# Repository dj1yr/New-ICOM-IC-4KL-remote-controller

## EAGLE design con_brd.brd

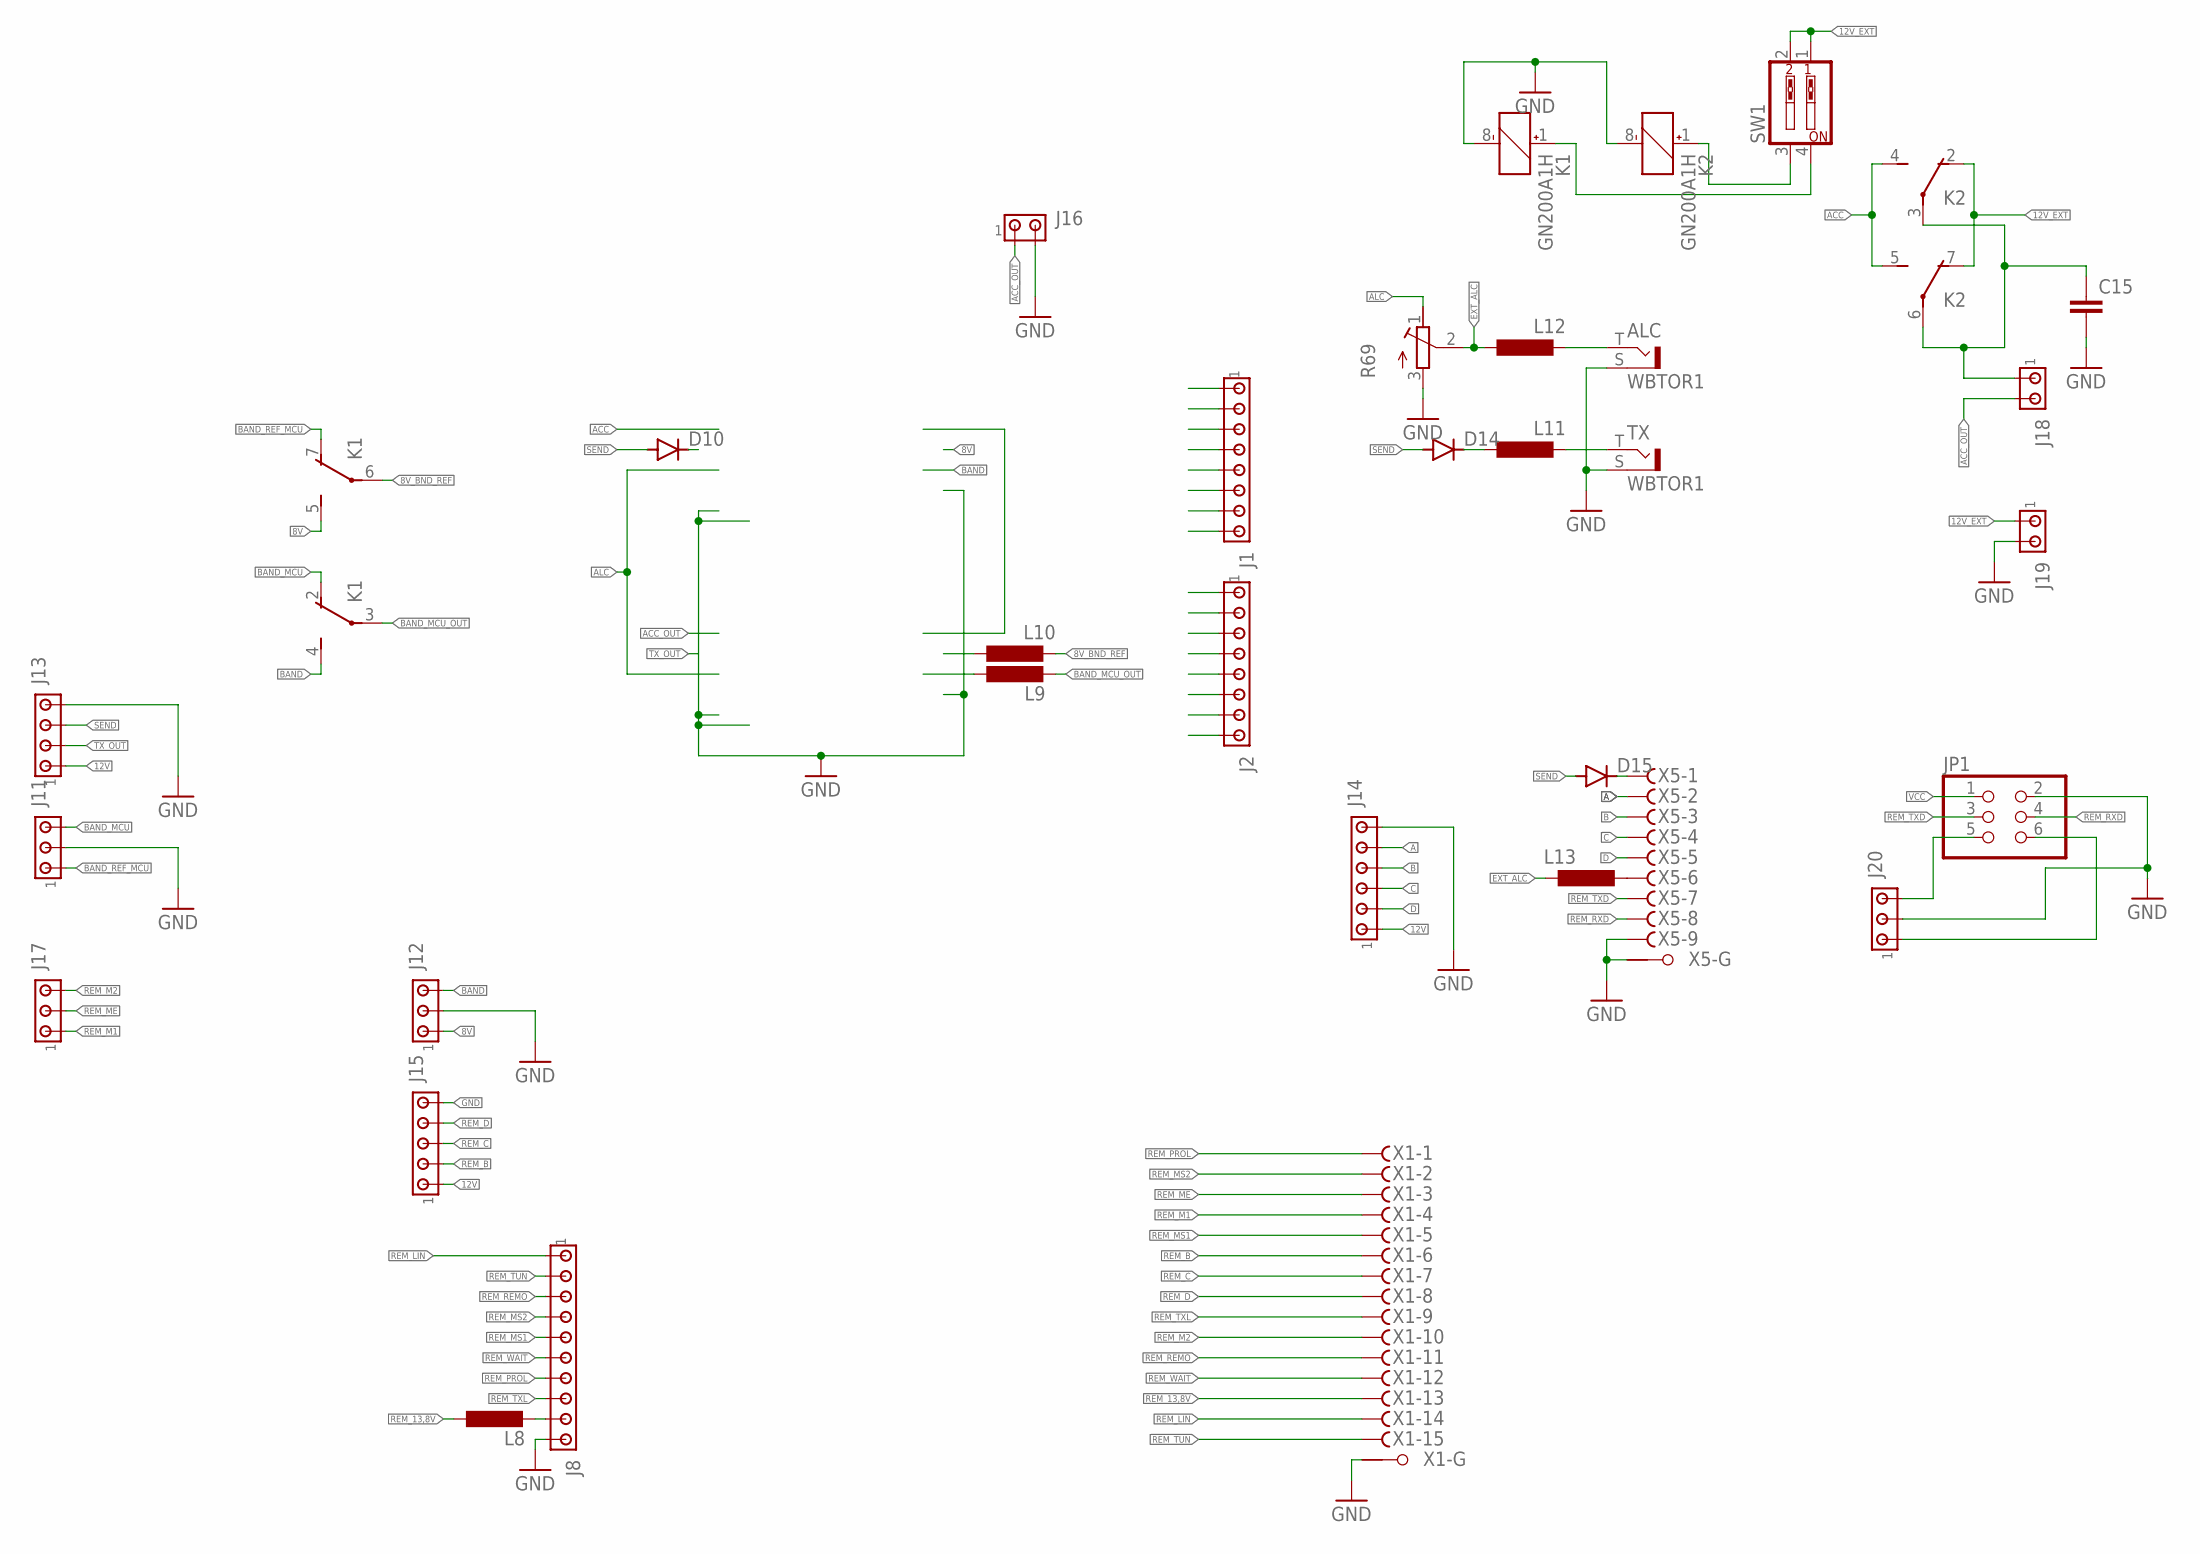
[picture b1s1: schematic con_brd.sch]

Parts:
ALC: WBTOR1
C15: C-EUC0805K; C0805K
D10, D14, D15: DIODE-SOD123; SOD123
J1, J2: MTA08-100; 10X08MTA
J8: MTA10-100; 10X10MTA
J11, J12, J17, J20: MTA03-100; 10X03MTA
J13: MTA04-100; 10X04MTA
J14: MTA06-100; 10X06MTA
J15: MTA05-100; 10X05MTA
J16, J18, J19: MTA02-100; 10X02MTA
JP1: PINHD-2X3; 2X03
K1, K2: GN200A1H; GN-A
L8: L-EUL3230M; L3230M
L9, L10, L11, L12, L13: L-EUL2012C; L2012C
R69: R-TRIMM43P; RTRIM43P
SW1: SW_DIP-2; EDG-02
TX: WBTOR1
X1: F15HPS; F15HP
X5: F09HPS; F09HP

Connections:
8V: J1.1, J12.1, K1.5 (S)
8V_BND_REF: K1.6, L10.2
12V: J13.1, J14.1, J15.1
12V_EXT: J19.1, K2.2 (O), K2.7 (O), SW1.1, SW1.2
A: J14.5, X5.2 (F)
ACC: J1.7, K2.4 (S), K2.5 (S)
ACC_OUT: J2.7, J16.1, J18.2
ALC: J1.5, J2.5, R69.1 (E)
B: J14.4, X5.3 (F)
BAND: J1.4, J12.3, K1.4 (S)
BAND_MCU: J11.3, K1.2 (O)
BAND_MCU_OUT: K1.3, L9.2
BAND_REF_MCU: J11.1, K1.7 (O)
C: J14.3, X5.4 (F)
D: J14.2, X5.5 (F)
EXT_ALC: L12.1, L13.1, R69.2 (S)
GND: ALC.S, C15.2, J1.2, J1.8, J2.2, J2.8, J8.10, J11.2, J12.2, J13.4, J14.6, J15.5, J16.2, J19.2, J20.2, JP1.2, K1.8 (-), K2.8 (-), R69.3 (A), TX.S, X1.G1, X5.9 (F), X5.G1; also elsewhere on the board
unnamed: J1.6, J2.6
unnamed: J2.4, L9.1
unnamed: J2.1, L10.1
unnamed: L11.2, TX.T
unnamed: ALC.T, L12.2
unnamed: D10.C, J1.3
unnamed: D14.C, L11.1
unnamed: D15.C, X5.1 (F)
unnamed: L13.2, X5.6 (F)
unnamed: J20.3, JP1.5
unnamed: J8.9, L8.2
unnamed: K2.1 (+), SW1.3
unnamed: K1.1 (+), SW1.4
unnamed: J20.1, JP1.6
REM_13,8V: L8.1, X1.13 (F)
REM_B: J15.2, X1.6 (F)
REM_C: J15.3, X1.7 (F)
REM_D: J15.4, X1.8 (F)
REM_LIN: J8.1, X1.14 (F)
REM_M1: J17.1, X1.4 (F)
REM_M2: J17.3, X1.10 (F)
REM_ME: J17.2, X1.3 (F)
REM_MS1: J8.5, X1.5 (F)
REM_MS2: J8.4, X1.2 (F)
REM_PROL: J8.7, X1.1 (F)
REM_REMO: J8.3, X1.11 (F)
REM_RXD: JP1.4, X5.8 (F)
REM_TUN: J8.2, X1.15 (F)
REM_TXD: JP1.3, X5.7 (F)
REM_TXL: J8.8, X1.9 (F)
REM_WAIT: J8.6, X1.12 (F)
SEND: D10.A, D14.A, D15.A, J13.3
TX_OUT: J2.3, J13.2
VCC: C15.1, J18.1, JP1.1, K2.3, K2.6

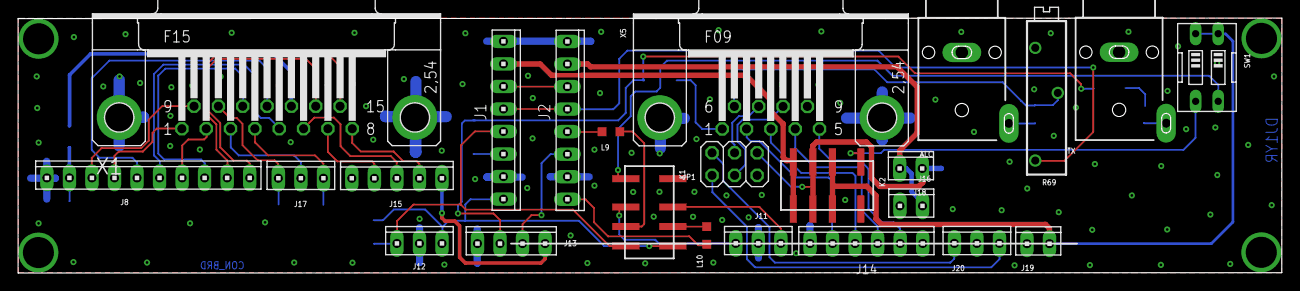
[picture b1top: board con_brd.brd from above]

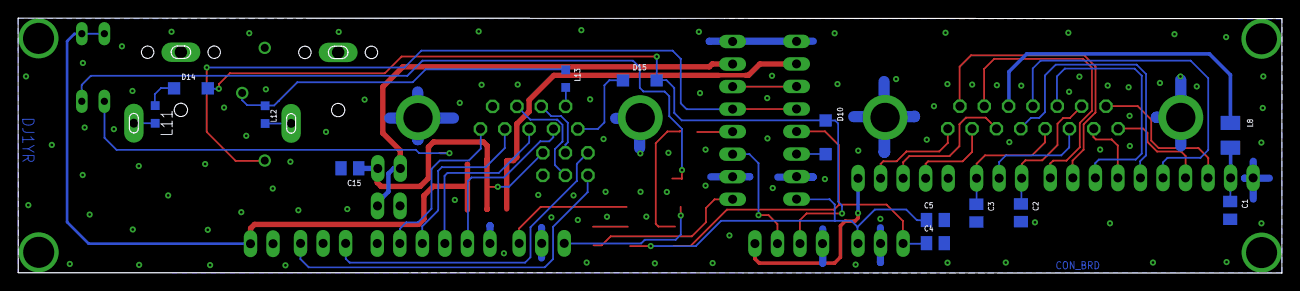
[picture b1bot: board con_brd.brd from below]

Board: 2 copper layers, 142.4 x 28.7 mm, 37 parts (13 on the bottom side), 51 nets.

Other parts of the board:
C1, C2, C3, C4, C5: C0805K

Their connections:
GND: C1.2, C2.2, C3.2, C4.2, C5.2; also elsewhere on the board

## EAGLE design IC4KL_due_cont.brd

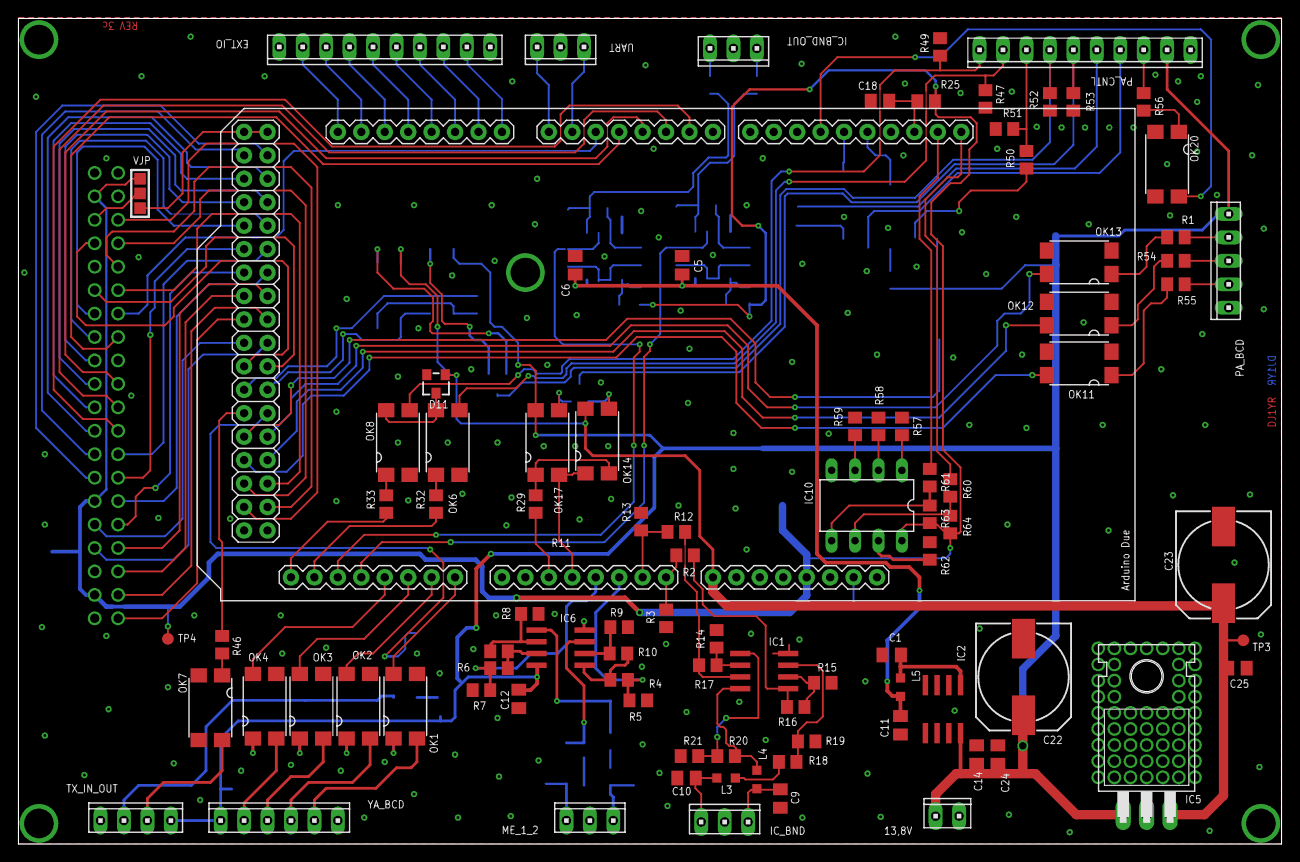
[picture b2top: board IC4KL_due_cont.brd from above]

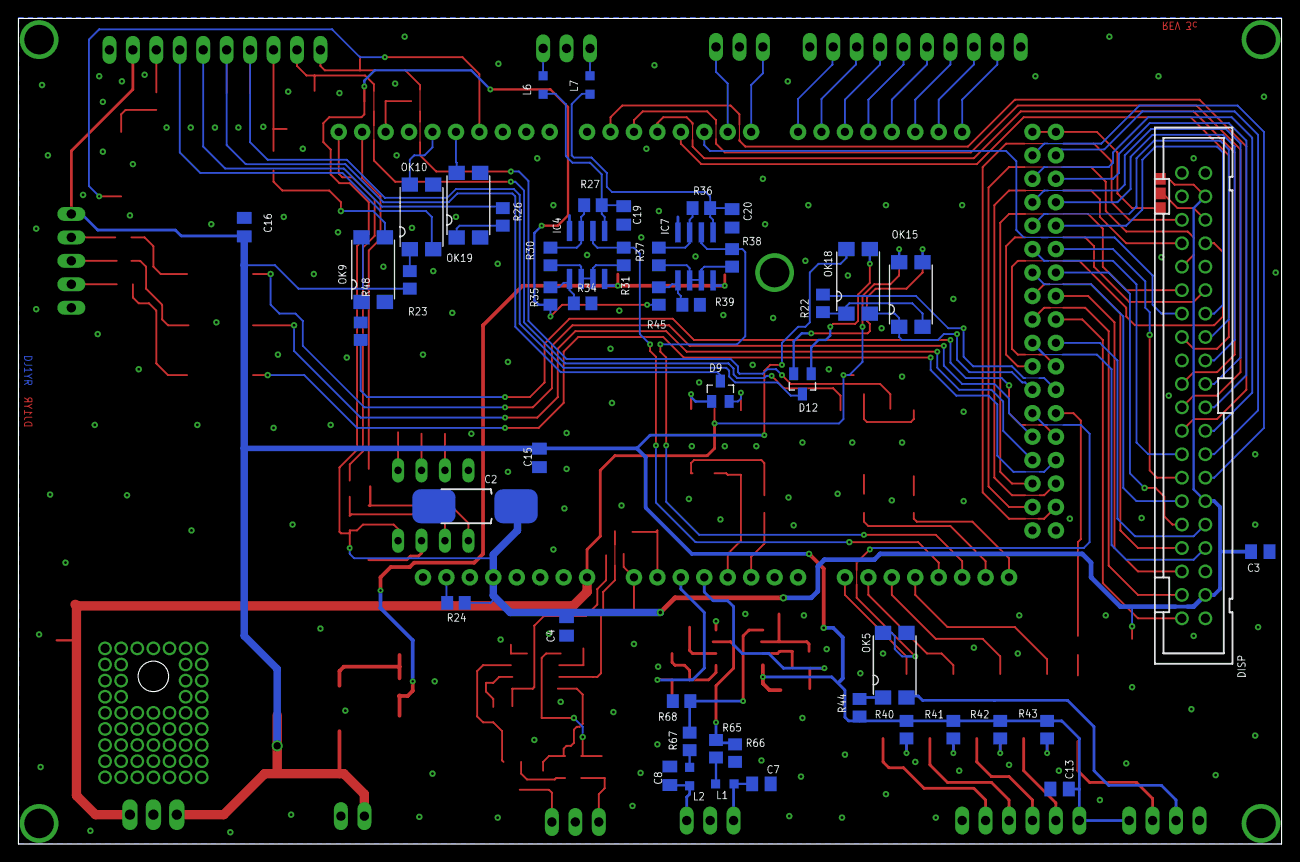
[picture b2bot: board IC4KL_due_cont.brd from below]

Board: 2 copper layers, 136.9 x 89.4 mm, 139 parts (49 on the bottom side), 92 nets.

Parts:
13,8V: 10X02MTA
C1, C3, C4, C5, C6, C7, C8, C9, C10, C11, C12, C13, C14, C15, C16, C18, C19, C20, C24, C25: C0805K
C2: 085CS_1AW
C22, C23: 150CLZ-1010
D9, D12: SOT23
D11: BZX84CSMD; TO236
DISP: 2540-; PAK100/2500-40
EXT_IO: 10X10MTA
IC1, IC4, IC6, IC7: LM358D; SO08
IC2: 78L10SMD; SO08
IC5: 7805T; TO220H
IC10: AT24CP; DIL08
IC_BND: 10X03MTA
IC_BND_OUT: 10X03MTA
L1, L2, L3, L4, L5, L6, L7: L2012C
ME_1_2: 10X03MTA
OK1, OK2, OK3, OK4, OK5, OK6, OK7, OK8, OK9, OK10, OK11, OK12, OK13, OK14, OK15, OK17, OK18, OK19, OK20: SFH6186-3; SMD4
PA_BCD: 10X05MTA
PA_CNTL: 10X10MTA
R1, R2, R4, R6, R10, R11, R12, R16, R17, R18, R20, R22, R23, R26, R29, R32, R33, R40, R41, R42, R43, R44, R48, R54, R55, R56, R57, R58, R59, R60, R61, R62, R63, R64, R65, R67: 1k; R0805
R3, R5, R7, R13: 1.8k; R0805
R8, R9, R14, R15: 220k; R0805
R19, R21: 10k; R0805
R24, R25, R50: 10; R0805
R27, R31, R36, R38, R47, R49, R51, R52, R53: 100k; R0805
R30, R34, R35, R37, R39, R45: 22k; R0805
R46: 390R; R0805
R66, R68: 2k2; R0805
TP3, TP4: TPB1,27; B1,27
TX_IN_OUT: 10X04MTA
UART: 10X03MTA
YA_BCD: 10X06MTA

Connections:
3.3V: C2.+, C3.1, C4.1, DISP.3, DISP.11, DISP.37, IC10.8, R24.2, R25.1, R35.1, R45.1, R63.2, R64.2, TP4.TP
5VIN: C23.+, C25.1, D11.A, DISP.35, IC5.3, OK14.4, OK15.4, TP3.TP
10V_BND_OPV: C5.1, C6.1, IC1.8, IC4.8, IC7.8
12V: 13,8V.2, C12.2, C13.2, C14.1, C15.2, C16.2, C22.+, C24.1, EXT_IO.1, IC2.8, IC5.1, IC6.8, OK9.4, OK17.4, OK18.4, PA_BCD.1, PA_CNTL.9, R23.1, R40.2, R41.2, R42.2, R43.2, R44.2, TX_IN_OUT.1, YA_BCD.6
DAC_IC_BND_OUT: IC4.2, R31.1
DAC_IC_BND_REF_OUT: IC7.2, R38.1
GND: 13,8V.1, C1.2, C2.-, C3.2, C4.2, C5.2, C6.2, C7.1, C8.2, C9.2, C10.1, C11.2, C12.1, C13.1, C14.2, C15.1, C16.1, C18.1, C19.2, C20.2, C22.-, C23.-, C24.2, C25.2, DISP.1, EXT_IO.10, IC1.4, IC2.2, IC2.3, IC2.6, IC2.7, IC4.4, IC5.2, IC6.4, IC7.4, IC10.4, IC_BND.2, IC_BND_OUT.2, ME_1_2.2, OK1.3, OK2.3, OK3.3, OK4.3, OK5.3, OK6.2, OK7.2, OK7.3, OK8.2, OK9.2, OK10.3, OK11.2, OK11.3, OK12.2, OK12.3, OK13.2, OK13.3, OK19.2, OK19.3, OK20.2, OK20.3, PA_BCD.5, PA_CNTL.10, R3.1, R5.1, R7.2, R8.2, R9.2, R13.2, R14.2, R15.2, R19.1, R21.1, R34.2, R39.2, R47.2, R49.2, R51.2, R52.2, R53.2, R57.1, R58.1, R59.1, R62.1, R66.1, R68.1, TX_IN_OUT.4, UART.2, YA_BCD.1
IC_BND: R2.1, R3.2
IC_BND_IN: C10.2, IC_BND.3, L3.1
IC_BND_OUT: IC_BND_OUT.3, L6.2
IC_BND_REF_IN: C9.1, IC_BND.1, L4.1
IC_BND_REF_OUT: IC_BND_OUT.1, L7.2
LINEAR: OK8.3, PA_CNTL.1, R49.1
M1: C7.2, L1.1, ME_1_2.3
M2: C8.1, L2.1, ME_1_2.1
ME1: R4.1, R5.2
ME2: R6.1, R7.1
MS1: D9.3, PA_CNTL.5, R53.1
MS2: D12.3, PA_CNTL.4, R52.1
unnamed: L2.2, R67.2
unnamed: IC6.1, R4.2, R10.2
unnamed: OK1.1, R40.1
unnamed: L1.2, R65.1
unnamed: IC6.7, R6.2, R11.2
unnamed: IC6.6, R8.1, R11.1
unnamed: IC6.2, R9.1, R10.1
unnamed: OK13.1, R1.1
unnamed: PA_BCD.2, R1.2
unnamed: IC1.1, R2.2, R16.2
unnamed: IC1.7, R12.2, R17.2
unnamed: IC1.6, R14.1, R17.1
unnamed: IC1.2, R15.1, R16.1
unnamed: IC7.3, R36.2, R37.1
unnamed: IC1.3, R18.2, R19.2
unnamed: L4.2, R20.2
unnamed: L3.2, R18.1
unnamed: D12.1, OK18.3
unnamed: C1.1, IC2.1, L5.1
unnamed: OK6.1, R32.2
unnamed: OK8.1, R33.2
unnamed: D11.C, OK6.4, OK8.4
unnamed: IC4.3, R27.2, R30.1
unnamed: OK15.2, OK18.1, R22.1
unnamed: IC1.5, R20.1, R21.2
unnamed: C19.1, IC4.1, L6.1, R27.1
unnamed: D12.2, OK15.3
unnamed: IC4.6, IC4.7, R30.2, R31.2
unnamed: D9.2, OK17.3
unnamed: D9.1, OK14.3
unnamed: IC7.6, IC7.7, R37.2, R38.2
unnamed: IC4.5, R34.1, R35.2
unnamed: OK2.1, R41.1
unnamed: OK10.1, R23.2
unnamed: OK3.1, R42.1
unnamed: OK14.2, OK17.1, R29.2
unnamed: OK4.1, R43.1
unnamed: C18.2, R25.2
unnamed: OK19.1, R26.2
unnamed: OK7.1, R46.2
unnamed: IC7.5, R39.1, R45.2
unnamed: OK20.1, R56.2
unnamed: C20.1, IC7.1, L7.1, R36.1
unnamed: OK5.1, R44.1
unnamed: OK5.2, TX_IN_OUT.3
unnamed: OK7.4, TX_IN_OUT.2
unnamed: OK9.3, R50.1
unnamed: PA_BCD.3, R54.2
unnamed: OK9.1, R48.2
unnamed: PA_BCD.4, R55.2
unnamed: OK12.1, R54.1
unnamed: OK11.1, R55.1
unnamed: IC10.3, R59.2
unnamed: IC10.2, R58.2
unnamed: IC10.1, R57.2
unnamed: IC10.7, R62.2
unnamed: IC10.5, R61.2, R63.1
unnamed: IC10.6, R60.2, R64.1
PRO: OK15.1, OK18.2
PROL: OK10.2, PA_CNTL.7
PS_ON: PA_CNTL.3, R50.2, R51.1
S$2: R67.1, R68.2
S$3: R65.2, R66.2
S$4: C11.1, L5.2
S$5: R12.1, R13.1
SWR: OK14.1, OK17.2
TUNER: OK6.3, PA_CNTL.2, R47.1
TXL: PA_CNTL.8, R56.1
WAIT: PA_CNTL.6, R26.1
Y_A: OK1.2, YA_BCD.2
Y_B: OK2.2, YA_BCD.3
Y_C: OK3.2, YA_BCD.4
Y_D: OK4.2, YA_BCD.5
